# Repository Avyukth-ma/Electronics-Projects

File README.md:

# Electronics-Projects
Collection of electronics, embedded systems, and PCB design projects

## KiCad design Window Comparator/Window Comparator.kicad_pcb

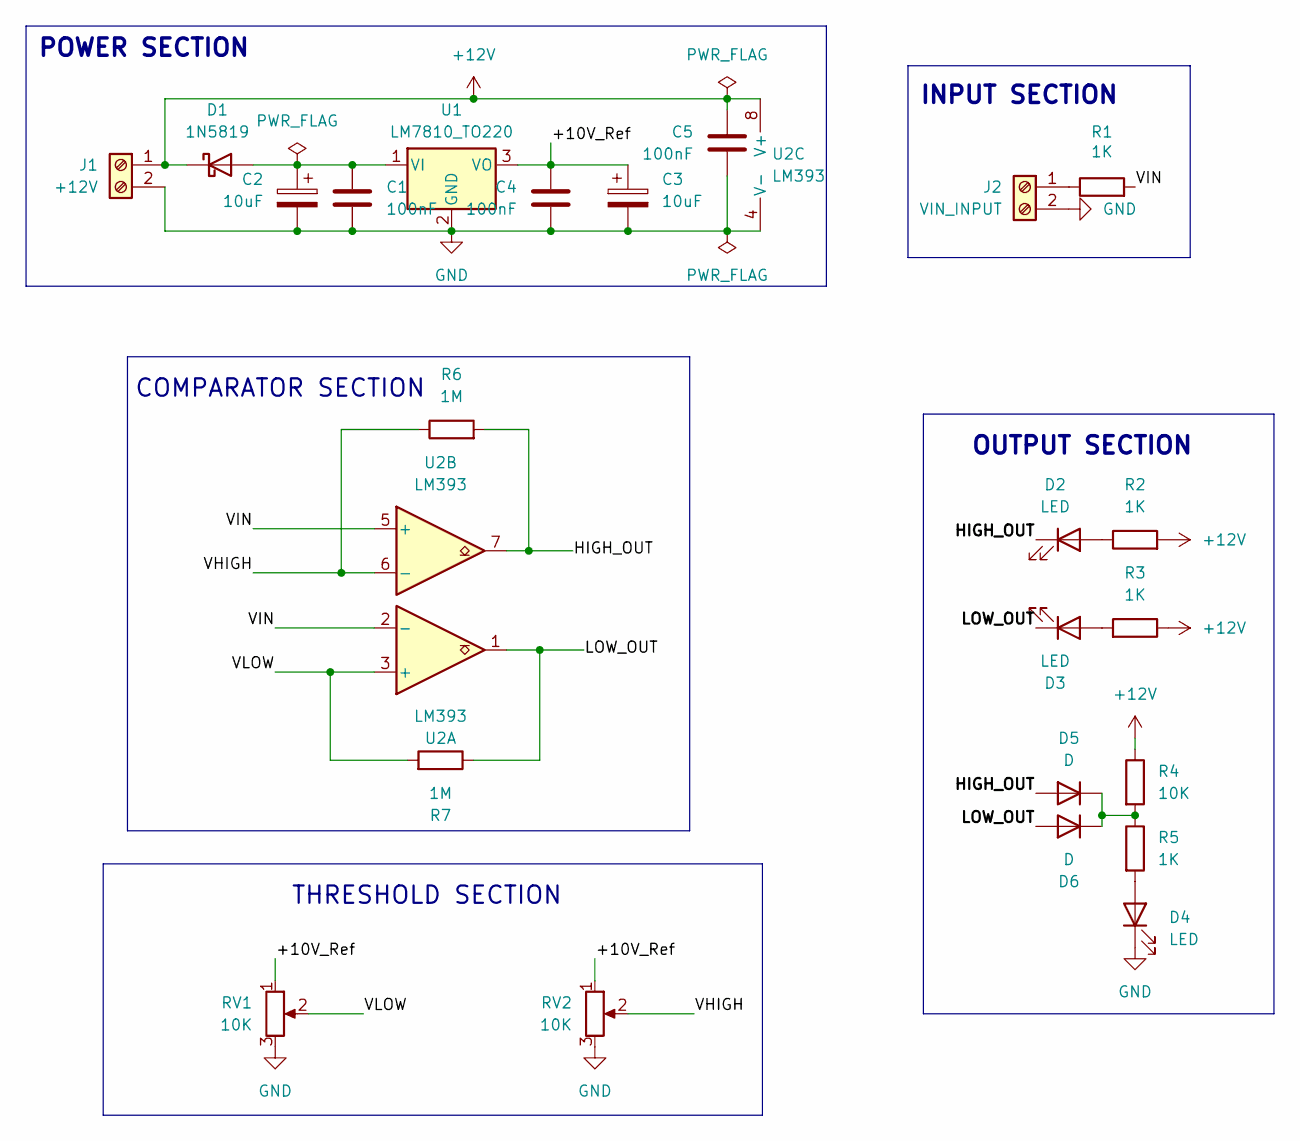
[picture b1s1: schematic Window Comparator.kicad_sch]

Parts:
C1, C4, C5: 100nF; C_Disc_D5.0mm_W2.5mm_P5.00mm
C2, C3: 10uF; CP_Radial_D5.0mm_P2.00mm
D1: 1N5819; D_DO-41_SOD81_P10.16mm_Horizontal
D2, D3, D4: LED; LED_D5.0mm
D5, D6: D; LED_D5.0mm
J1: +12V; PinHeader_1x02_P2.54mm_Vertical
J2: VIN_INPUT; PinHeader_1x02_P2.54mm_Vertical
R1, R2, R3, R5: 1K; R_Axial_DIN0207_L6.3mm_D2.5mm_P7.62mm_Horizontal
R4: 10K; R_Axial_DIN0207_L6.3mm_D2.5mm_P7.62mm_Horizontal
R6, R7: 1M; R_Axial_DIN0207_L6.3mm_D2.5mm_P7.62mm_Horizontal
RV1, RV2: 10K; Potentiometer_Bourns_3296W_Vertical
U1: LM7810_TO220; TO-220-3_Vertical
U2: LM393; DIP-8_W7.62mm

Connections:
+12V: C5.1, D1.1 (K), J1.1, R2.2, R3.1, R4.1, U2.8 (V+)
/+10V_Ref: C3.1, C4.1, RV1.1, RV2.1, U1.3 (VO)
/HIGH_OUT: D2.1 (K), D5.2 (A), R6.2, U2.7
/LOW_OUT: D3.1 (K), D6.2 (A), R7.1, U2.1
/VHIGH: R6.1, RV2.2, U2.6 (-)
/VIN: R1.2, U2.2 (-), U2.5 (+)
/VLOW: R7.2, RV1.2, U2.3 (+)
GND: C1.2, C2.2, C3.2, C4.2, C5.2, D4.1 (K), J1.2, J2.2, RV1.3, RV2.3, U1.2 (GND), U2.4 (V-)
unnamed: C1.1, C2.1, D1.2 (A), U1.1 (VI)
unnamed: D2.2 (A), R2.1
unnamed: D3.2 (A), R3.2
unnamed: D4.2 (A), R5.2
unnamed: D5.1 (K), D6.1 (K), R4.2, R5.1
unnamed: J2.1, R1.1

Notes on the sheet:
INPUT SECTION
THRESHOLD SECTION
OUTPUT SECTION
COMPARATOR SECTION
POWER SECTION

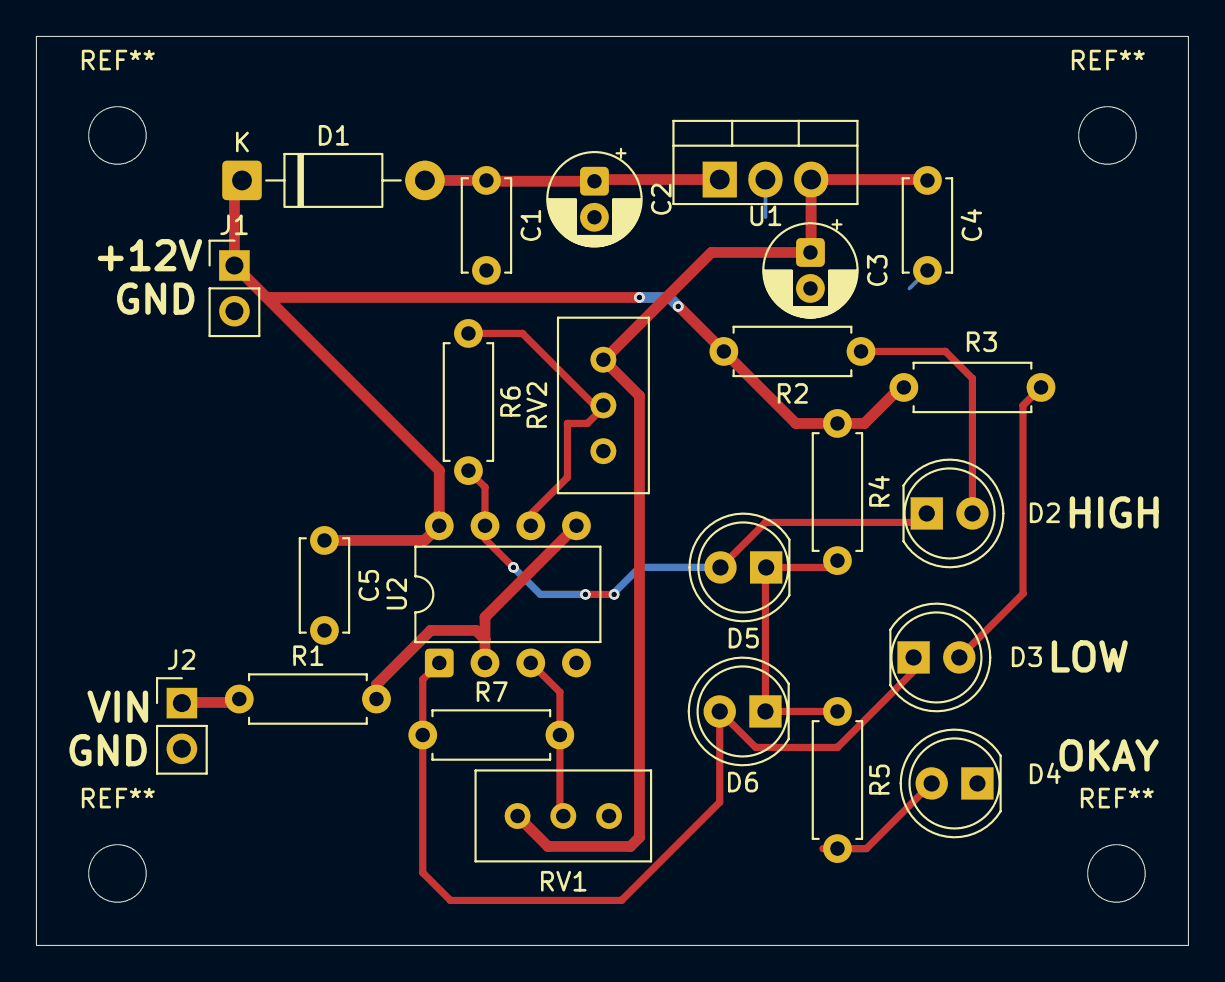
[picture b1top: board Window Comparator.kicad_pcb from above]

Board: 2 copper layers, 64.0 x 50.5 mm, 24 parts (0 on the bottom side), 14 nets.

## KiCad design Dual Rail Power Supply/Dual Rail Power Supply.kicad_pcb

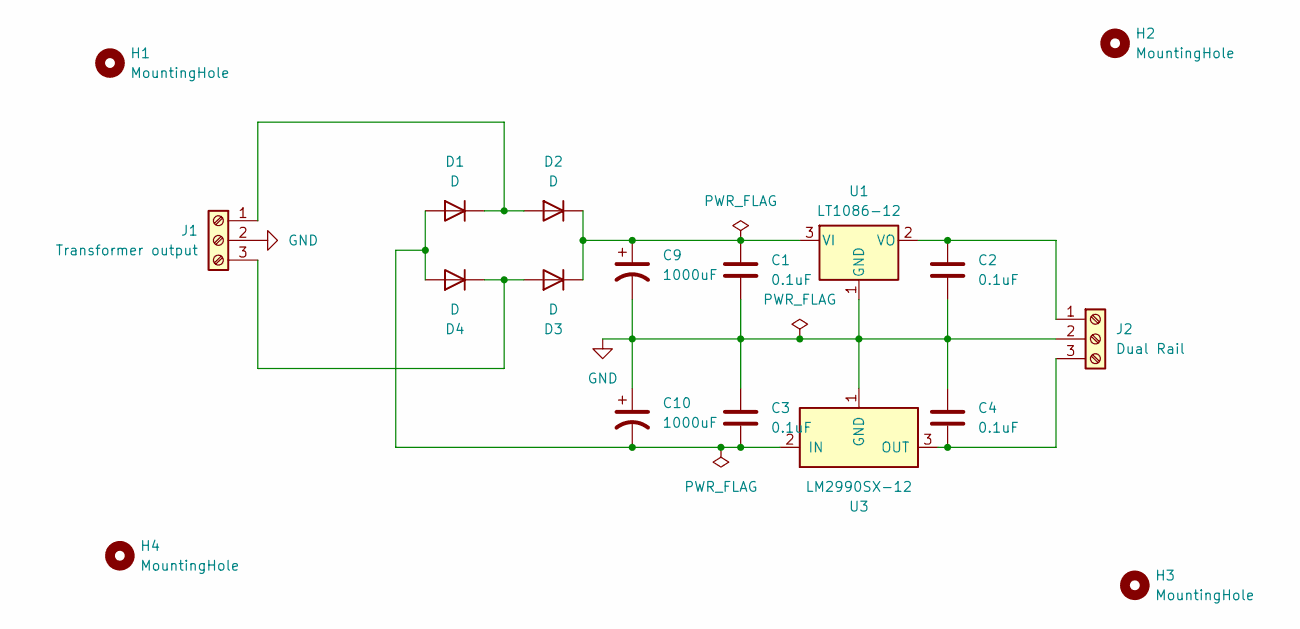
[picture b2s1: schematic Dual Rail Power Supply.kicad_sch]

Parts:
C1, C2, C3, C4: 0.1uF; C_0805_2012Metric_Pad1.18x1.45mm_HandSolder
C9, C10: 1000uF; CP_Elec_10x10.5
D1, D2, D3, D4: D; D_SMA
H1, H2, H3, H4: MountingHole; MountingHole_3.2mm_M3
J1: Transformer output; TerminalBlock_Phoenix_MKDS-1,5-3-5.08_1x03_P5.08mm_Horizont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
J2: Dual Rail; TerminalBlock_Phoenix_MKDS-1,5-3-5.08_1x03_P5.08mm_Horizont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
U1: LT1086-12; TO-252-2
U3: LM2990SX-12; TO-263-3_TabPin2

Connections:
GND: C1.2, C2.2, C3.1, C4.1, C9.2, C10.1, J1.2, J2.2, U1.1 (GND), U3.1 (GND)
unnamed: C3.2, C10.2, D1.2 (A), D4.2 (A), U3.2 (IN)
unnamed: D1.1 (K), D2.2 (A), J1.1
unnamed: C1.1, C9.1, D2.1 (K), D3.1 (K), U1.3 (VI)
unnamed: D3.2 (A), D4.1 (K), J1.3
unnamed: C2.1, J2.1, U1.2 (VO)
unnamed: C4.2, J2.3, U3.3 (OUT)

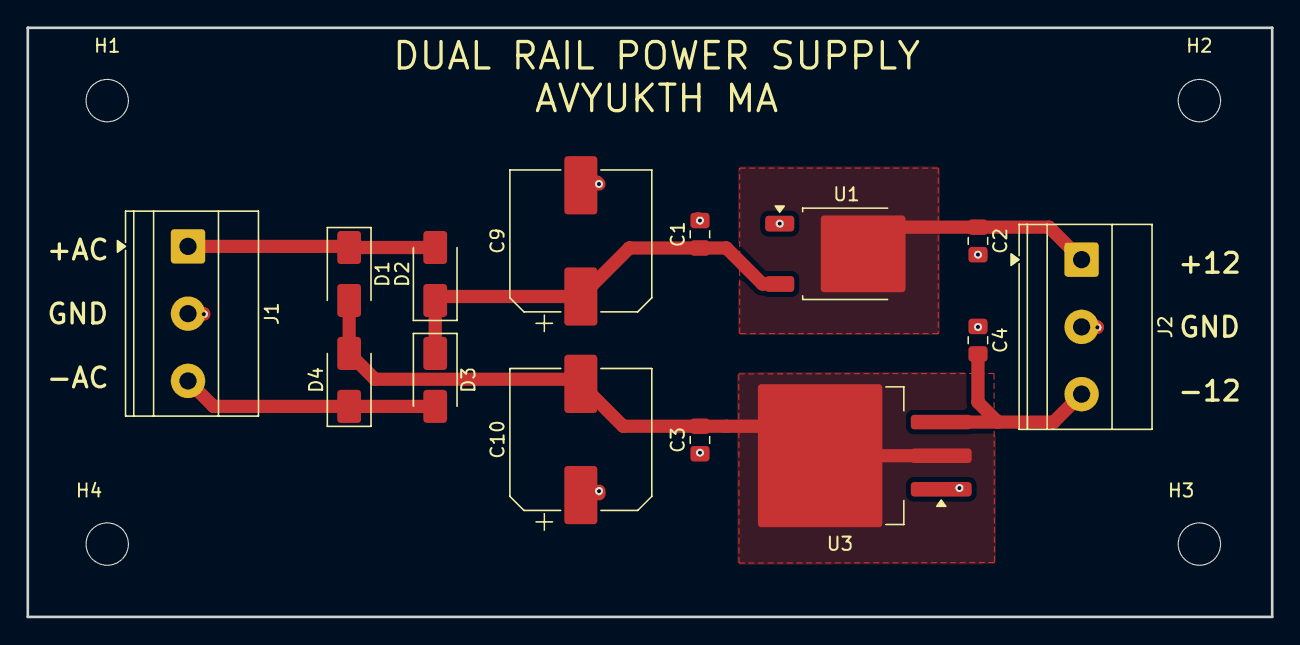
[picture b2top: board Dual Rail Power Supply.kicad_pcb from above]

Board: 2 copper layers, 94.0 x 44.5 mm, 18 parts (0 on the bottom side), 7 nets.

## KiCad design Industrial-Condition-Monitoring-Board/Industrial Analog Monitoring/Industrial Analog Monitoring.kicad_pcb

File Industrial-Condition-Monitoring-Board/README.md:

# Industrial Condition Monitoring Board

## Overview

An analog multi-sensor condition monitoring PCB designed during an Analog Electronics internship at Yuken India Ltd.

The project demonstrates analog signal conditioning, amplification, filtering, threshold detection, hysteresis, power supply design, and PCB development using KiCad.

## Sensors

- LM35 Temperature Sensor
- LDR Light Sensor
- Potentiometer (Process Variable Simulator)

## Features

- Temperature monitoring with multi-level indication
- Light monitoring with threshold detection
- Simulated process variable monitoring
- Analog signal conditioning
- Comparator-based decision making
- Schmitt trigger hysteresis
- 5V regulated power supply
- Custom PCB design

## Tools

- KiCad
- Git
- GitHub

## Project Status

Stage 1: Architecture Finalization (In Progress)

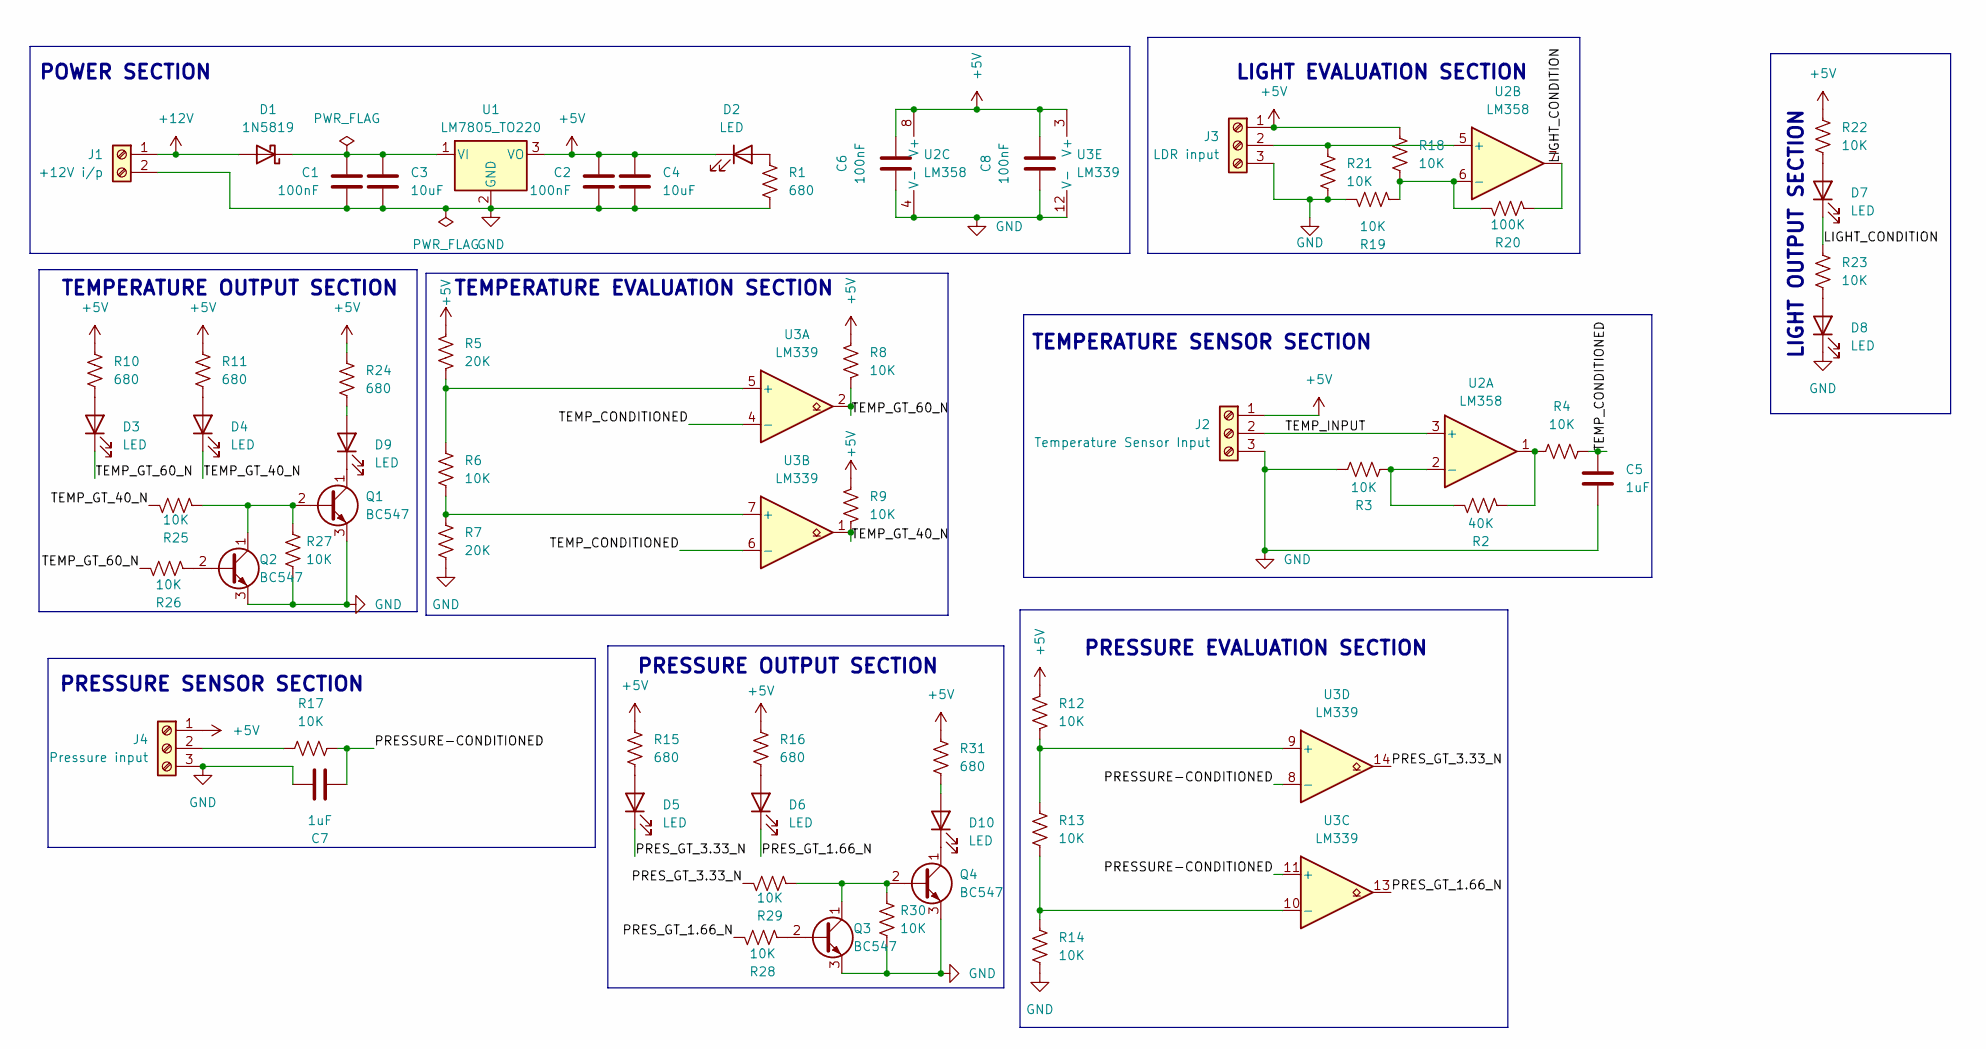
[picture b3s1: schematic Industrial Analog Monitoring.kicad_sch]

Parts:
C1, C2, C6, C8: 100nF; C_0805_2012Metric
C3, C4: 10uF; C_1206_3216Metric
C5, C7: 1uF; C_1206_3216Metric
D1: 1N5819; D_DO-41_SOD81_P10.16mm_Horizontal
D2, D3, D4, D5, D6, D7, D8, D9, D10: LED; LED_1206_3216Metric
J1: +12V i/p; TerminalBlock_Phoenix_MKDS-1,5-2-5.08_1x02_P5.08mm_Horizont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
J2: Temperature Sensor Input; TerminalBlock_Phoenix_MKDS-1,5-3-5.08_1x03_P5.08mm_Horizont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
J3: LDR input; TerminalBlock_Phoenix_MKDS-1,5-3-5.08_1x03_P5.08mm_Horizont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
J4: Pressure input; TerminalBlock_Phoenix_MKDS-1,5-3-5.08_1x03_P5.08mm_Horizont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
Q1, Q2, Q3, Q4: BC547; TO-92_Inline
R1, R10, R11, R15, R16, R24, R31: 680; R_0805_2012Metric
R2: 40K; R_0805_2012Metric
R3, R4, R6, R8, R9, R12, R13, R14, R17, R18, R19, R21, R22, R23, R25, R26, R27, R28, R29, R30: 10K; R_0805_2012Metric
R5, R7: 20K; R_0805_2012Metric
R20: 100K; R_0805_2012Metric
U1: LM7805_TO220; TO-220-3_Vertical
U2: LM358; SOIC-8_3.9x4.9mm_P1.27mm
U3: LM339; SOIC-14_3.9x8.7mm_P1.27mm

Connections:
+5V: C2.1, C4.1, C6.2, C8.2, D2.1 (K), J2.1, J3.1, J4.1, R5.1, R8.1, R9.1, R10.1, R11.1, R12.1, R15.1, R16.1, R18.1, R22.1, R24.1, R31.1, U1.3 (VO), U2.8 (V+), U3.3 (V+)
+12V: D1.2 (A), J1.1
/LIGHT_CONDITION: D7.1 (K), R20.1, R23.1, U2.7
/PRESSURE-CONDITIONED: C7.2, R17.2, U3.8 (-), U3.11 (+)
/PRES_GT_1.66_N: D6.1 (K), R28.1, U3.13
/PRES_GT_3.33_N: D5.1 (K), R29.1, U3.14
/TEMP_CONDITIONED: C5.1, R4.2, U3.4 (-), U3.6 (-)
/TEMP_GT_40_N: D4.1 (K), R9.2, R25.1, U3.1
/TEMP_GT_60_N: D3.1 (K), R8.2, R26.1, U3.2
/TEMP_INPUT: J2.2, U2.3 (+)
GND: C1.2, C2.2, C3.2, C4.2, C5.2, C6.1, C7.1, C8.1, D8.1 (K), J1.2, J2.3, J3.3, J4.3, Q1.3 (E), Q2.3 (E), Q3.3 (E), Q4.3 (E), R1.2, R3.1, R7.2, R14.2, R19.2, R21.2, R27.1, R30.1, U1.2 (GND), U2.4 (V-), U3.12 (V-)
unnamed: C1.1, C3.1, D1.1 (K), U1.1 (VI)
unnamed: D2.2 (A), R1.1
unnamed: D3.2 (A), R10.2
unnamed: D4.2 (A), R11.2
unnamed: D5.2 (A), R15.2
unnamed: D6.2 (A), R16.2
unnamed: D7.2 (A), R22.2
unnamed: D8.2 (A), R23.2
unnamed: D9.2 (A), R24.2
unnamed: D9.1 (K), Q1.1 (C)
unnamed: D10.2 (A), R31.2
unnamed: D10.1 (K), Q4.1 (C)
unnamed: J3.2, R21.1, U2.5 (+)
unnamed: J4.2, R17.1
unnamed: Q1.2 (B), Q2.1 (C), R25.2, R27.2
unnamed: Q2.2 (B), R26.2
unnamed: Q3.2 (B), R28.2
unnamed: Q3.1 (C), Q4.2 (B), R29.2, R30.2
unnamed: R2.2, R4.1, U2.1
unnamed: R2.1, R3.2, U2.2 (-)
unnamed: R18.2, R19.1, R20.2, U2.6 (-)
unnamed: R5.2, R6.1, U3.5 (+)
unnamed: R6.2, R7.1, U3.7 (+)
unnamed: R13.2, R14.1, U3.10 (-)
unnamed: R12.2, R13.1, U3.9 (+)

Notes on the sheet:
LIGHT OUTPUT SECTION
PRESSURE OUTPUT SECTION
TEMPERATURE OUTPUT SECTION
TEMPERATURE EVALUATION SECTION
PRESSURE SENSOR SECTION
LIGHT EVALUATION SECTION
POWER SECTION
PRESSURE EVALUATION SECTION
TEMPERATURE SENSOR SECTION

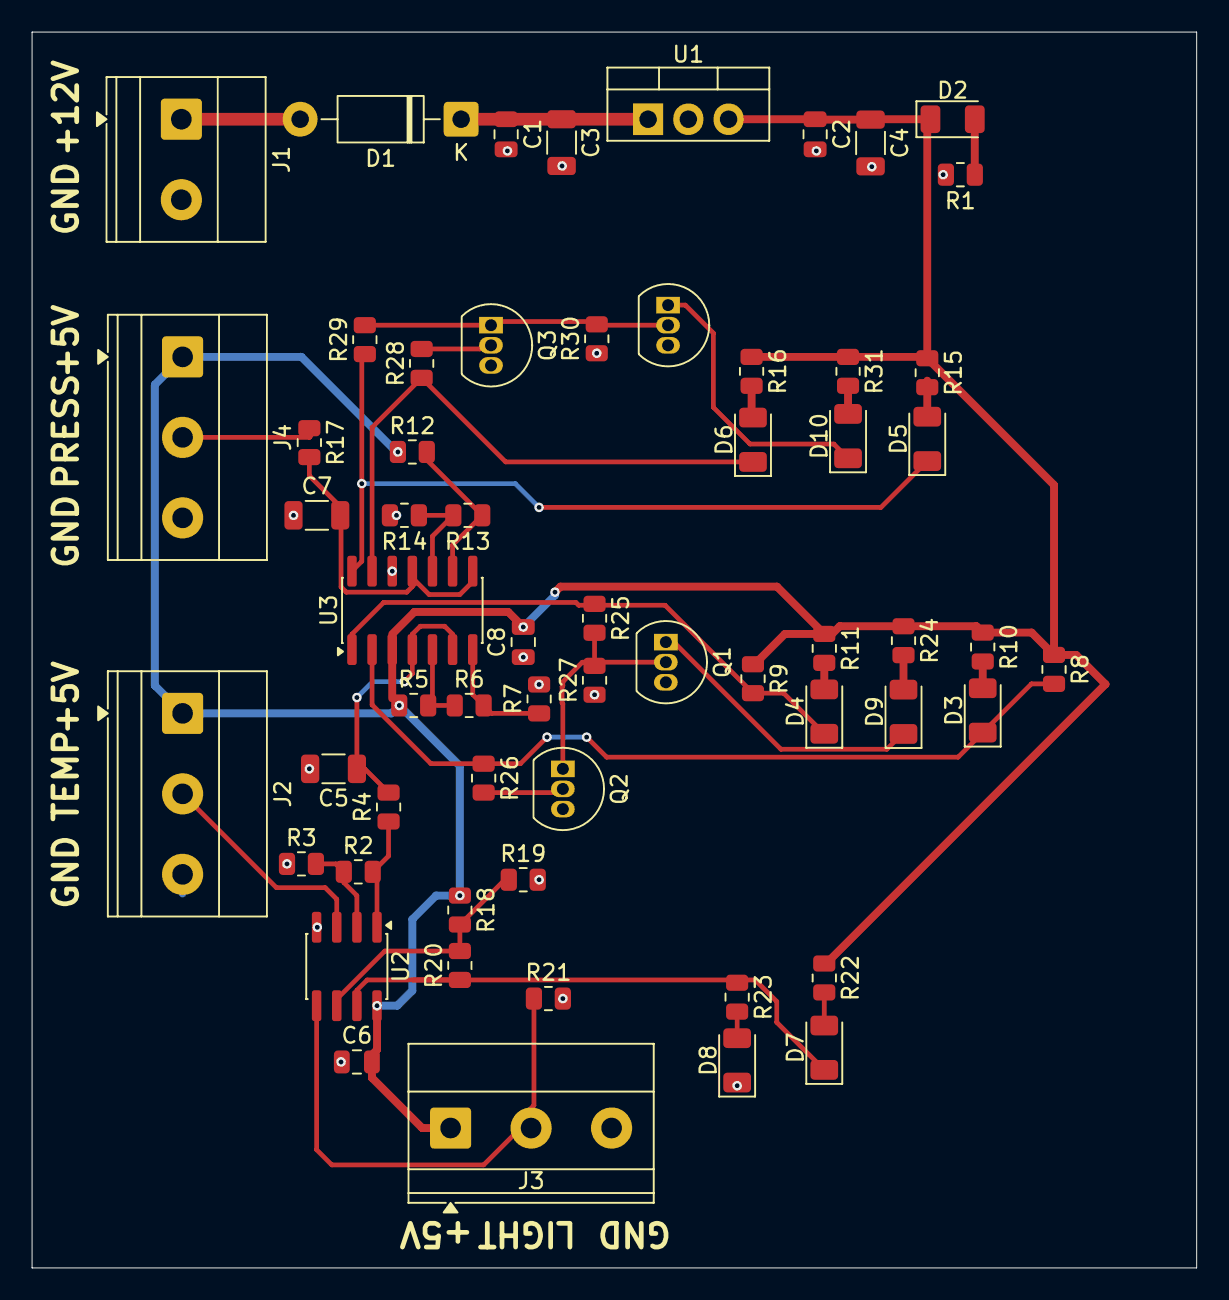
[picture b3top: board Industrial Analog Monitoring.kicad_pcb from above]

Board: 2 copper layers, 73.5 x 78.0 mm, 60 parts (0 on the bottom side), 36 nets.

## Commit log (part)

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2026-06-05 Initialize Industrial Condition Monitoring Board project
2026-06-05 Add initial project documentation
2026-06-09 Revise design log with project updates and status
    Updated the design log to reflect project progress, including architecture finalization, component selection, PCB layout, and verification.
2026-06-15 fix: Correctly integrated DAQ node source code
2026-06-20 Added Industrial Condition Monitoring Board project
2026-06-20 Updated project
2026-06-20 Updated the project name
